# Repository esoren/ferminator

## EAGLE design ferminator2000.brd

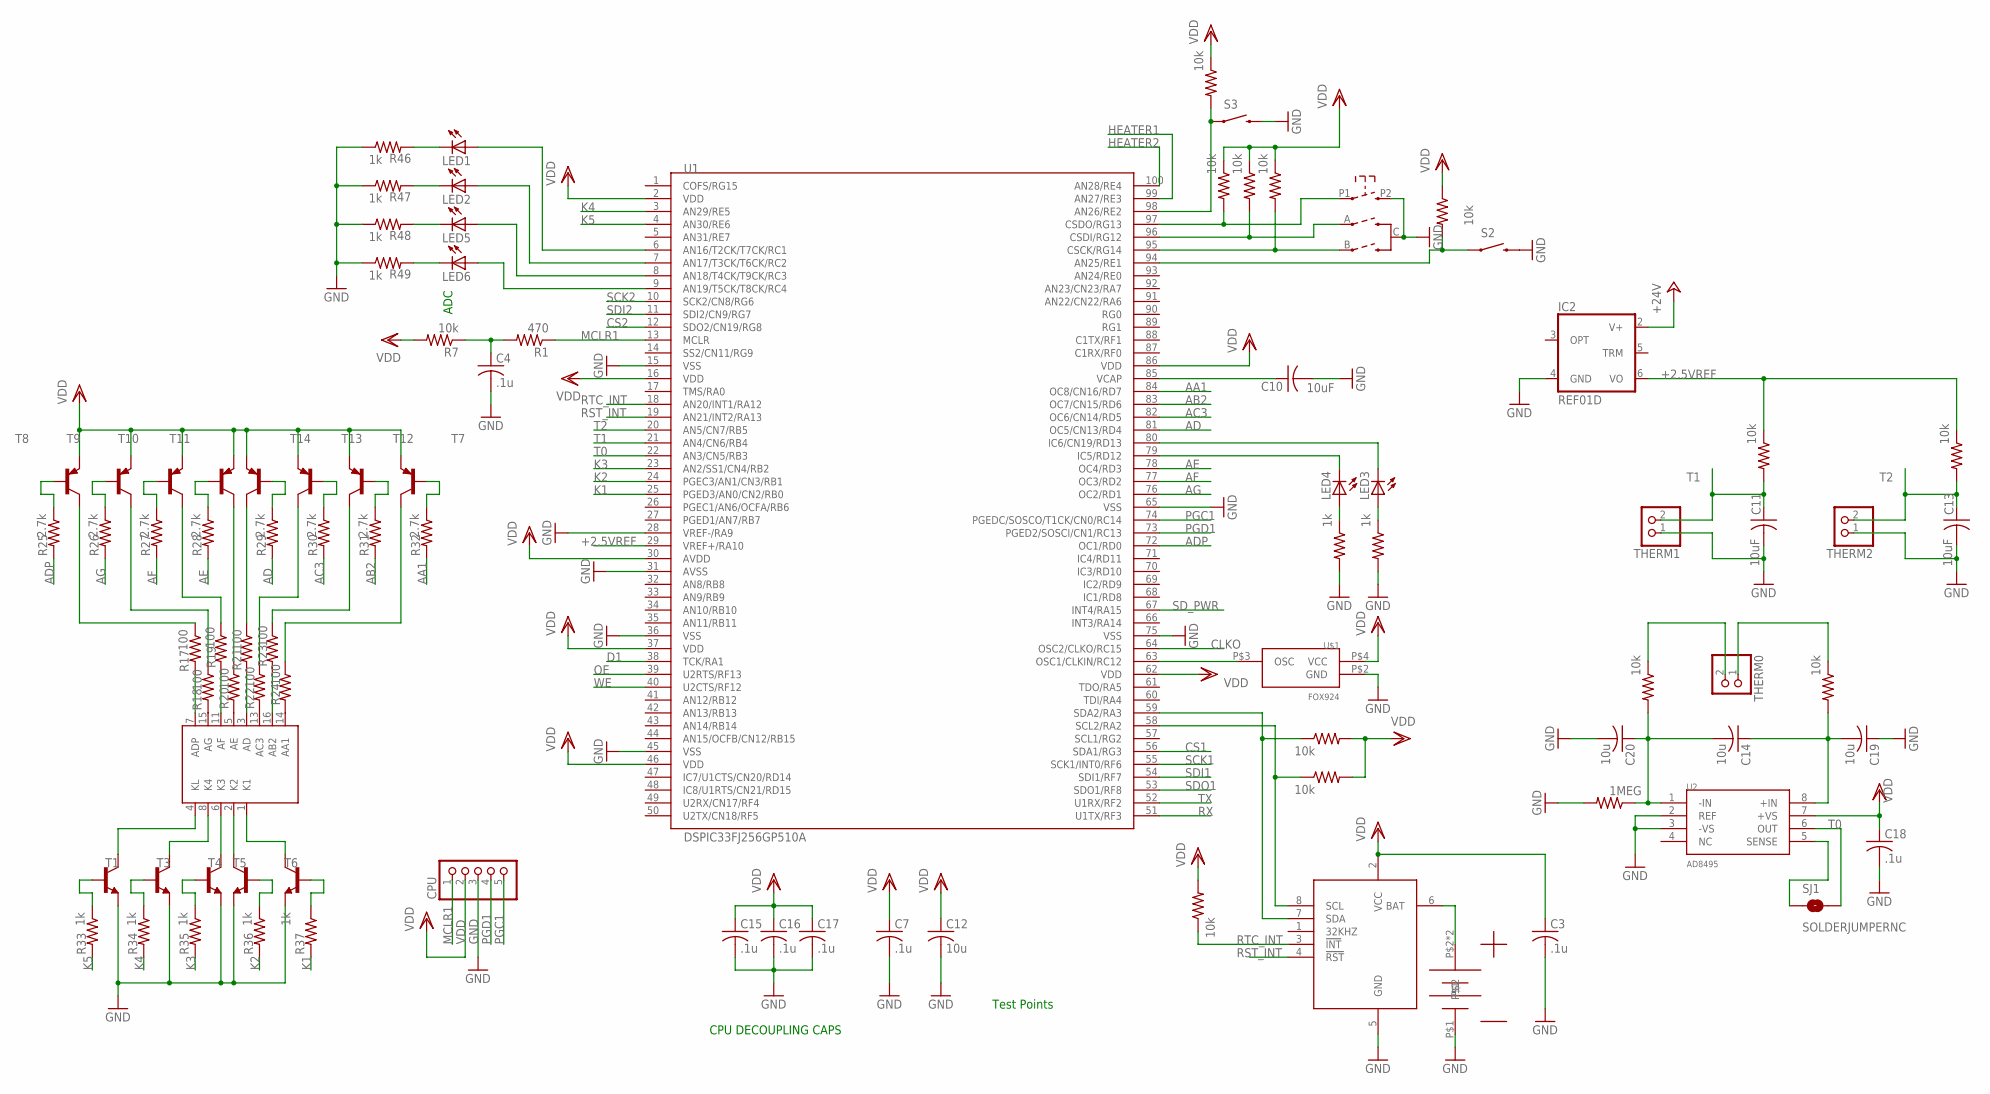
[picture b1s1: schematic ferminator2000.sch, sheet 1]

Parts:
C3, C4, C7, C15, C16, C17, C18: .1u; C0603
C10, C11, C13: 10uF; C0805
C12: 10u; C0805
C14, C19, C20: 10u; C0603
CPU: PINHD-1X5; 1X05
IC2: REF01D; SO08
LED1, LED2, LED3, LED4, LED5, LED6: LEDCHIP-LED0805; CHIP-LED0805
R1: 470; R0805
R7, R38, R39, R41, R42, R43, R44, R45, R50, R51, R52, R53, R54: 10k; R0805
R14, R15, R33, R34, R35, R36, R37, R46, R47, R48, R49: 1k; R0805
R17, R18, R19, R20, R21, R22, R23, R24: 100; R0805
R25, R26, R27, R28, R29, R30, R31, R32: 2.7k; R0805
R40: 1MEG; R0805
S2, S3: SWITCH-MOMENTARY-2; TACTILE_SWITCH_TALL
SJ1: SOLDERJUMPERNC; SJ_2S
SW1: ENCODER_SW1-PEC12; PEC12_INCREMENTAL_ENCODER
T1, T3, T4, T5, T6: MMBT3904LT1-NPN-SOT23-BEC; SOT23-BEC
T7, T8, T9, T10, T11, T12, T13, T14: MMBT3906LT1-PNP-SOT23-BEC; SOT23-BEC
THERM0, THERM1, THERM2: PINHD-1X2; 1X02
U1: DSPIC33FJ256GP510A; TQFP100
U2: AD8495; MSOP8
U$1: FOX924; CRYSTAL
U$2: 12MM_BATTER_HOLDER; 12.5MMCOILCELLHOLDER
U$5: DS3231; SOIC8
U$7: LTC-4027JRLTC-4027JR; LTC-4727JR

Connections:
1: R17.1, T8.C
2: R18.1, T9.C
3: R19.1, T10.C
4: R20.1, T11.C
5: R21.1, T14.C
6: R22.1, T13.C
7: R23.1, T12.C
8: R24.1, T7.C
+2.5VREF: IC2.6 (VO), R38.1, R39.1, U1.29 (VREF+/RA10)
+24V: IC2.2 (V+); also elsewhere on the board
AA1: R32.2, U1.84 (OC8/CN16/RD7)
AA1_BASE: R32.1, T7.B
AB2: R31.2, U1.83 (OC7/CN15/RD6)
AB2_BASE: R31.1, T12.B
AC3: R30.2, U1.82 (OC6/CN14/RD5)
AC3_BASE: R30.1, T13.B
AD: R29.2, U1.81 (OC5/CN13/RD4)
ADP: R25.2, U1.72 (OC1/RD0)
ADP_BASE: R25.1, T8.B
AD_BASE: R29.1, T14.B
AE: R28.2, U1.78 (OC4/RD3)
AE_BASE: R28.1, T11.B
AF: R27.2, U1.77 (OC3/RD2)
AF_BASE: R27.1, T10.B
AG: R26.2, U1.76 (OC2/RD1)
AG_BASE: R26.1, T9.B
CLKIN: U1.63 (OSC1/CLKIN/RC12), U$1.P$3 (OSC)
CLKO: U1.64 (OSC2/CLKO/RC15)
CS1: U1.56 (SDA1/RG3); also elsewhere on the board
CS2: U1.12 (SDO2/CN19/RG8)
D1: U1.38 (TCK/RA1)
GND: C3.2, C4.2, C7.2, C10.2, C11.2, C12.2, C13.2, C15.2, C16.2, C17.2, C18.2, C19.1, C20.2, CPU.3, IC2.4 (GND), R14.2, R15.2, R40.2, R46.1, R47.1, R48.1, R49.1, S2.B2 (2), S3.B2 (2), SW1.C, SW1.P2 (2), T1.E, T3.E, T4.E, T5.E, T6.E, THERM1.1, THERM2.1, U1.15 (VSS), U1.28 (VREF-/RA9), U1.31 (AVSS), U1.36 (VSS), U1.45 (VSS), U1.65 (VSS), U1.75 (VSS), U2.2 (REF), U2.3 (-VS), U$1.P$2 (GND), U$2.P$1, U$5.5 (GND); also elsewhere on the board
HEATER1: U1.99 (AN27/RE3); also elsewhere on the board
HEATER2: U1.100 (AN28/RE4); also elsewhere on the board
K1: R37.2, U1.25 (PGED3/AN0/CN2/RB0)
K2: R36.2, U1.24 (PGEC3/AN1/CN3/RB1)
K3: R35.2, U1.23 (AN2/SS1/CN4/RB2)
K3_BASE: R35.1, T4.B
K4: R34.2, U1.3 (AN29/RE5)
K4_BASE: R34.1, T3.B
K5: R33.2, U1.4 (AN30/RE6)
K5_BASE: R33.1, T1.B
MCLR1: CPU.1, R1.1, U1.13 (MCLR)
unnamed: LED3.A, R14.1
unnamed: LED4.A, R15.1
unnamed: C4.1, R1.2, R7.1
unnamed: C10.1, U1.85 (VCAP)
unnamed: LED4.C, U1.79 (IC5/RD12)
unnamed: LED3.C, U1.80 (IC6/CN19/RD13)
unnamed: T1.C, U$7.4 (KL)
unnamed: U$2.P$2, U$2.P$3, U$5.6 (BAT)
unnamed: R45.1, U1.59 (SDA2/RA3), U$5.7 (SDA)
unnamed: T3.C, U$7.8 (K4)
unnamed: T4.C, U$7.6 (K3)
unnamed: T5.C, U$7.2 (K2)
unnamed: T6.C, U$7.1 (K1)
unnamed: R18.2, U$7.15 (AG)
unnamed: C14.2, C20.1, R40.1, R41.2, U2.1 (-IN)
unnamed: C14.1, C19.2, R42.2, U2.8 (+IN)
unnamed: R41.1, THERM0.2
unnamed: R42.1, THERM0.1
unnamed: R36.1, T5.B
unnamed: R37.1, T6.B
unnamed: SJ1.1, U2.5 (SENSE)
unnamed: R43.2, S3.A2 (1), U1.98 (AN26/RE2)
unnamed: R20.2, U$7.5 (AE)
unnamed: R22.2, U$7.13 (AC3)
unnamed: R24.2, U$7.14 (AA1)
unnamed: R17.2, U$7.7 (ADP)
unnamed: R19.2, U$7.11 (AF)
unnamed: R44.2, S2.A2 (1), U1.94 (AN25/RE1)
unnamed: R21.2, U$7.3 (AD)
unnamed: R23.2, U$7.16 (AB2)
unnamed: LED6.A, U1.9 (AN19/T5CK/T8CK/RC4)
unnamed: LED5.A, U1.8 (AN18/T4CK/T9CK/RC3)
unnamed: LED2.A, U1.7 (AN17/T3CK/T6CK/RC2)
unnamed: LED1.A, U1.6 (AN16/T2CK/T7CK/RC1)
unnamed: LED1.C, R46.2
unnamed: LED2.C, R47.2
unnamed: LED5.C, R48.2
unnamed: LED6.C, R49.2
unnamed: R52.2, SW1.B, U1.95 (CSCK/RG14)
unnamed: R50.2, SW1.A, U1.96 (CSDI/RG12)
unnamed: R51.2, SW1.P1 (1), U1.97 (CSDO/RG13)
unnamed: R53.1, U1.58 (SCL2/RA2), U$5.8 (SCL)
OE: U1.39 (U2RTS/RF13)
PGC1: CPU.5, U1.74 (PGEDC/SOSCO/T1CK/CN0/RC14)
PGD1: CPU.4, U1.73 (PGED2/SOSCI/CN1/RC13)
RST_INT: U1.19 (AN21/INT2/RA13), U$5.4 (!RST)
RTC_INT: R54.1, U1.18 (AN20/INT1/RA12), U$5.3 (!INT)
RX: U1.51 (U1TX/RF3); also elsewhere on the board
SCK1: U1.55 (SCK1/INT0/RF6); also elsewhere on the board
SCK2: U1.10 (SCK2/CN8/RG6)
SDI1: U1.54 (SDI1/RF7); also elsewhere on the board
SDI2: U1.11 (SDI2/CN9/RG7)
SDO1: U1.53 (SDO1/RF8); also elsewhere on the board
SD_PWR: U1.67 (INT4/RA15); also elsewhere on the board
T0: SJ1.2, U1.22 (AN3/CN5/RB3), U2.6 (OUT)
T1: C11.1, R38.2, THERM1.2, U1.21 (AN4/CN6/RB4)
T2: C13.1, R39.2, THERM2.2, U1.20 (AN5/CN7/RB5)
TX: U1.52 (U1RX/RF2); also elsewhere on the board
VDD: C3.1, C7.1, C12.1, C15.1, C16.1, C17.1, C18.1, CPU.2, R7.2, R43.1, R44.1, R45.2, R50.1, R51.1, R52.1, R53.2, R54.2, T7.E, T8.E, T9.E, T10.E, T11.E, T12.E, T13.E, T14.E, U1.2 (VDD), U1.16 (VDD), U1.30 (AVDD), U1.37 (VDD), U1.46 (VDD), U1.62 (VDD), U1.86 (VDD), U2.7 (+VS), U$1.P$4 (VCC), U$5.2 (VCC); also elsewhere on the board
WE: U1.40 (U2CTS/RF12)

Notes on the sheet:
ADC
CPU DECOUPLING CAPS
Test Points

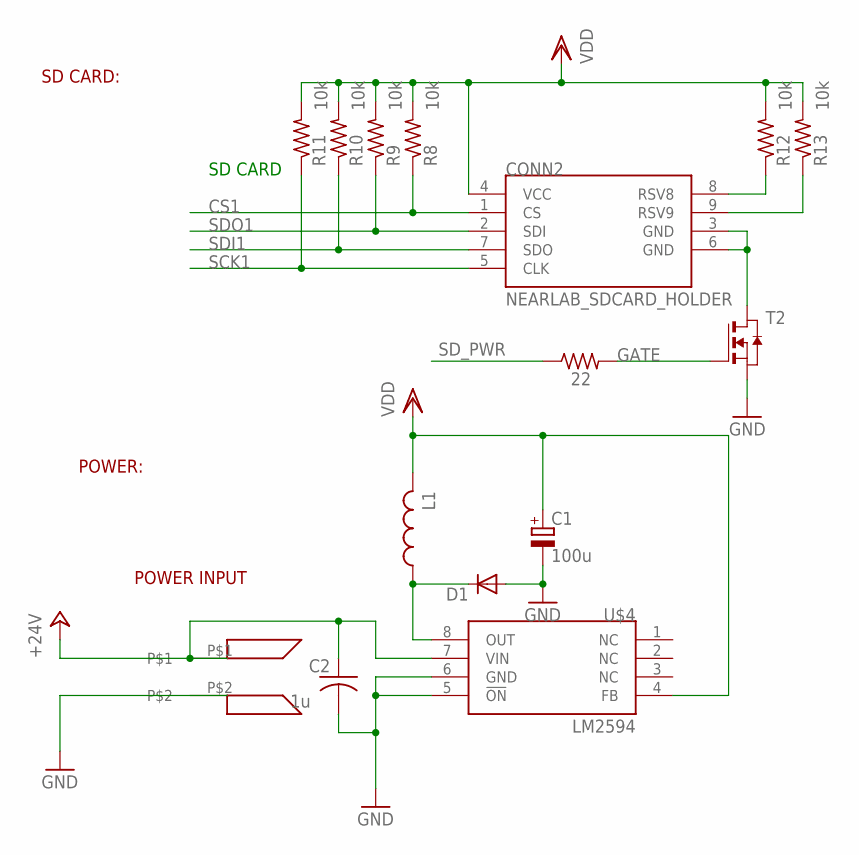
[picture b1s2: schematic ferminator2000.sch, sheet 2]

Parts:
C1: 100u; UD-6,3X5,8_NICHICON
C2: 1u; C0805
CONN2: NEARLAB_SDCARD_HOLDER; NEARLAB_DM1AA-SF-PEJ
D1: DIODE-SOD323-R; SOD323-R
L1: L-USL3225M; L3225M
R8, R9, R10, R11, R12, R13: 10k; R0805
R16: 22; R0805
T2: NMOSSOT23; SOT-23
U$3: PHOENIX-3.5MM; PHOENIX_3.5MM
U$4: LM2594; SOIC8

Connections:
+24V: C2.1, U$3.P$1, U$4.7 (VIN); also elsewhere on the board
CS1: CONN2.1 (CS), R8.1; also elsewhere on the board
GATE: R16.2, T2.3 (G)
GND: C1.-, C2.2, D1.A, T2.2 (S), U$3.P$2, U$4.5 (!ON), U$4.6 (GND); also elsewhere on the board
unnamed: CONN2.9 (RSV9), R13.1
unnamed: CONN2.8 (RSV8), R12.1
unnamed: CONN2.3 (GND), CONN2.6 (GND), T2.1 (D)
unnamed: D1.C, L1.1, U$4.8 (OUT)
SCK1: CONN2.5 (CLK), R11.1; also elsewhere on the board
SDI1: CONN2.7 (SDO), R10.1; also elsewhere on the board
SDO1: CONN2.2 (SDI), R9.1; also elsewhere on the board
SD_PWR: R16.1; also elsewhere on the board
VDD: C1.+, CONN2.4 (VCC), L1.2, R8.2, R9.2, R10.2, R11.2, R12.2, R13.2, U$4.4 (FB); also elsewhere on the board

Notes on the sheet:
SD CARD
SD CARD:
POWER:
POWER INPUT

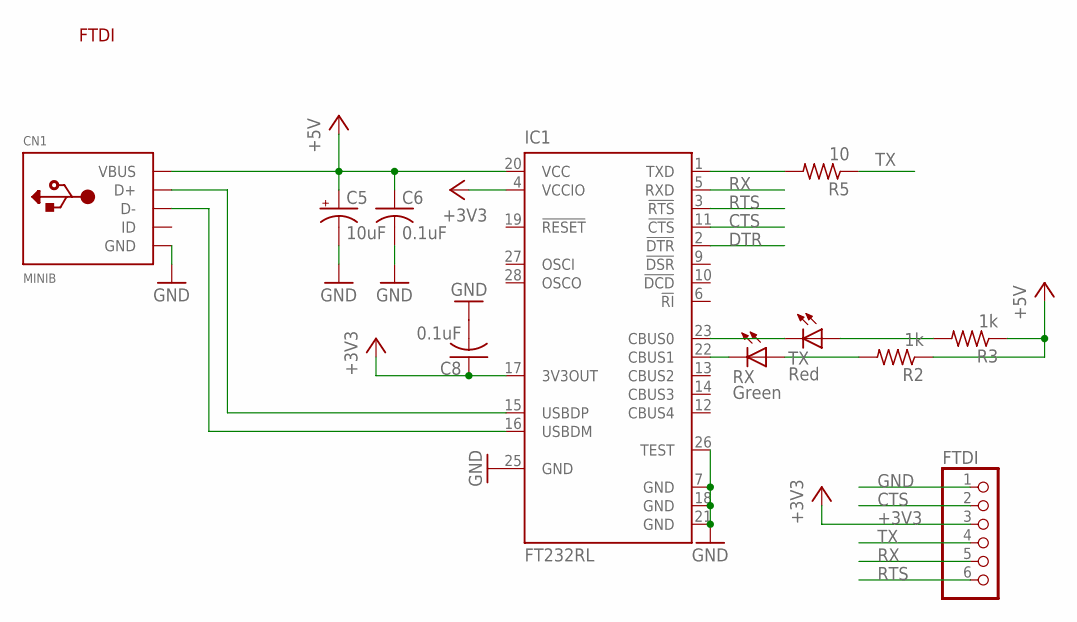
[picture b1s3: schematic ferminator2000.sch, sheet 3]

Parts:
C5: 10uF; A/3216-18R
C6, C8: 0.1uF; C0805K
CN1: MINIB; USB-MINIB
FTDI: PINHD-1X6CB; 1X06-CLEANBIG
IC1: FT232RL; SSOP28
R2, R3: 1k; R0805
R5: 10; R0805
RX: Green; CHIP-LED0805
TX: Red; CHIP-LED0805

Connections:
+3V3: C8.1, FTDI.3, IC1.4 (VCCIO), IC1.17 (3V3OUT)
+5V: C5.+, C6.1, CN1.VBUS, IC1.20 (VCC), R2.1, R3.1
CTS: FTDI.2, IC1.11 (!CTS)
DTR: IC1.2 (!DTR)
GND: C5.-, C6.2, C8.2, CN1.GND, FTDI.1, IC1.7 (GND), IC1.18 (GND), IC1.21 (GND), IC1.25 (GND), IC1.26 (TEST); also elsewhere on the board
unnamed: CN1.D+, IC1.15 (USBDP)
unnamed: CN1.D-, IC1.16 (USBDM)
unnamed: IC1.23 (CBUS0), TX.C
unnamed: IC1.22 (CBUS1), RX.C
unnamed: R2.2, RX.A
unnamed: R3.2, TX.A
unnamed: IC1.1 (TXD), R5.2
RTS: FTDI.6, IC1.3 (!RTS)
RX: FTDI.5, IC1.5 (RXD); also elsewhere on the board
TX: FTDI.4, R5.1; also elsewhere on the board

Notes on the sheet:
FTDI

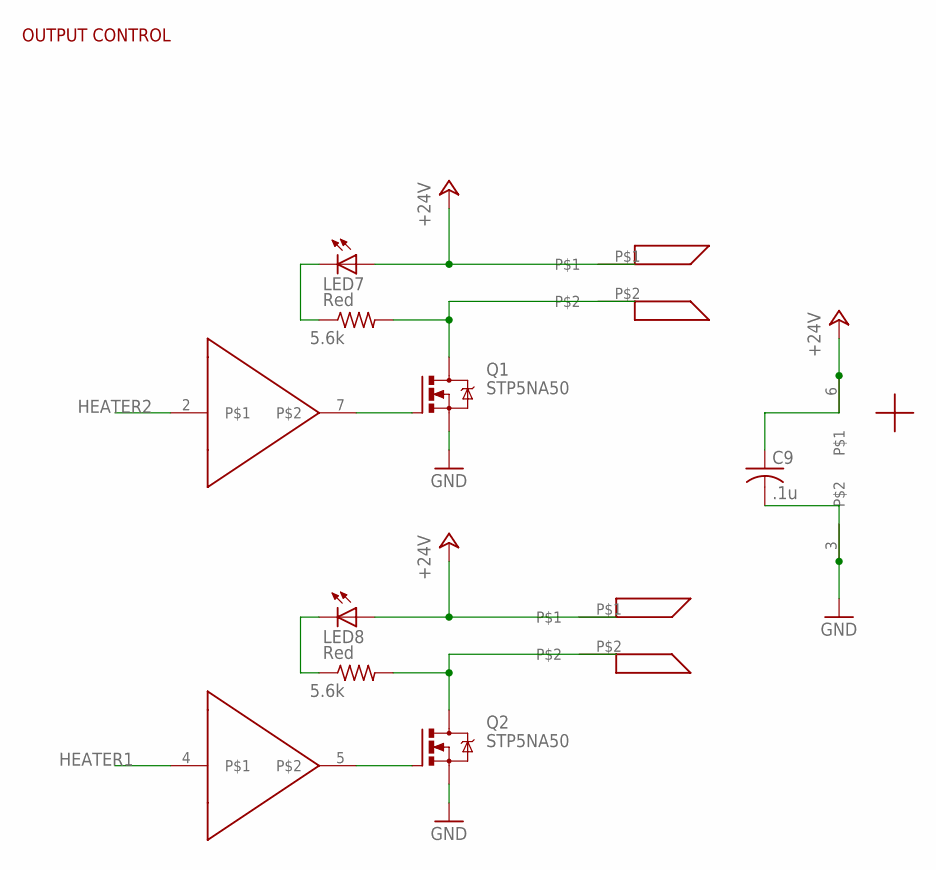
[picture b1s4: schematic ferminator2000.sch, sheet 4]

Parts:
C9: .1u; C0603
LED7, LED8: Red; CHIP-LED0805
Q1, Q2: STP5NA50; TO220BV
R4, R6: 5.6k; R0805
U$8, U$10: PHOENIX-3.5MM; PHOENIX_3.5MM
U$11: TC4427; SOIC8

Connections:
+24V: C9.1, LED7.A, LED8.A, U$8.P$1, U$10.P$1, U$11.6; also elsewhere on the board
GND: C9.2, Q1.S, Q2.S, U$11.3; also elsewhere on the board
HEATER1: U$11.4; also elsewhere on the board
HEATER2: U$11.2; also elsewhere on the board
unnamed: Q1.D, R4.2, U$10.P$2
unnamed: Q1.G, U$11.7
unnamed: Q2.G, U$11.5
unnamed: LED7.C, R4.1
unnamed: Q2.D, R6.2, U$8.P$2
unnamed: LED8.C, R6.1

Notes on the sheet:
OUTPUT CONTROL

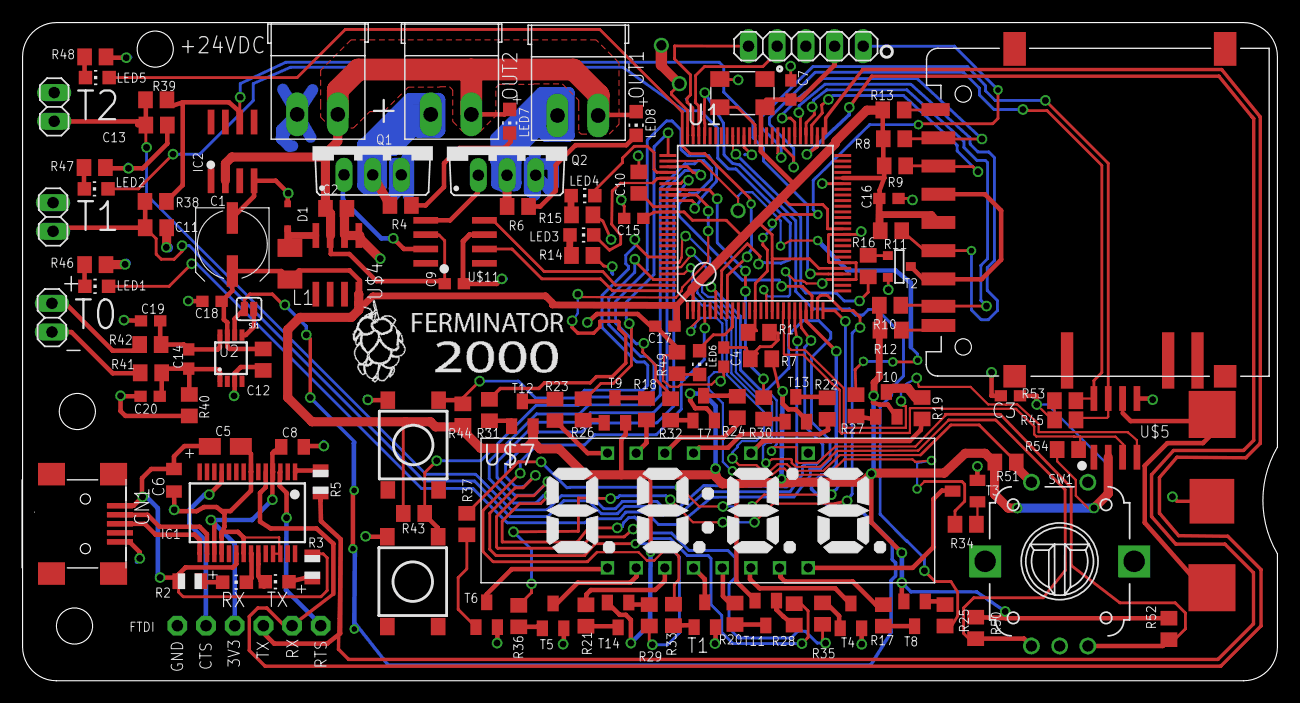
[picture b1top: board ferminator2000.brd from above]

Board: 2 copper layers, 111.1 x 58.3 mm, 126 parts (0 on the bottom side), 118 nets.

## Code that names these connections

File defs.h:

/*! \file defs.h
    \brief Contains all definitions
    
    
*/

#ifndef INC_DEFS_H
#define INC_DEFS_H


#define FCY 40000000UL ///40 MIPS operating speed (used for __delay_ms() and __delay_S())

#define BREAKPOINT Nop();Nop();Nop();
/** @defgroup LEDS LEDS
 * @{ */
#define T0_LED      LATCbits.LATC1
#define T0_LED_DIR  TRISCbits.TRISC1
#define T1_LED      LATCbits.LATC2
#define T1_LED_DIR  TRISCbits.TRISC2
#define T2_LED      LATCbits.LATC3
#define T2_LED_DIR  TRISCbits.TRISC3
#define LED3        LATDbits.LATD12
#define LED3_DIR    TRISDbits.TRISD12
#define LED4        LATDbits.LATD13
#define LED4_DIR    TRISDbits.TRISD13
#define LED6        LATCbits.LATC4
#define LED6_DIR     TRISCbits.TRISC4

/** @} */

/** @defgroup SD_PINS SD Pins
 * @{ */
#define SD_PWR 		LATAbits.LATA15
#define SD_PWR_DIR	TRISAbits.TRISA15		 
#define SDO1_PIN	LATFbits.LATF8
#define SDO1_PIN_DIR	TRISFbits.TRISF8
#define SDI1_PIN	PORTFbits.RF7
#define SDI1_PIN_DIR	TRISFbits.TRISF7
#define SCK1_PIN	LATFbits.LATF6
#define SCK1_PIN_DIR	TRISFbits.TRISF6
#define CS1_PIN		LATGbits.LATG3
#define CS1_PIN_DIR	TRISGbits.TRISG3
/** @} */

/** @defgroup HEATER_PINS HEATER Pins
 * @{ */
#define HEATER1_DIR     TRISEbits.TRISE3
#define HEATER1         LATEbits.LATE3
#define HEATER2_DIR     TRISEbits.TRISE4
#define HEATER2         LATEbits.LATE4

/** @} */


/** @defgroup ERROR_DEFS Error Definitions
 * @{ */
#define     GENERIC_ERROR			1 ///generic error flag
#define     SD_CARD_NOT_INITIALIZED		2 ///error initializing sd card
#define     BUFFER_OVERFLOW			3 ///buffer overflow
#define     BUFFER_POINTER			4 ///buffer pointer out of acceptable range
/** @} */

/** @defgroup TIMER_DEFS Timer Definitions
 * @{ */
#define TIMER2_ON		T2CONbits.TON  
#define TIMER2_PERIOD 	200   //3200 = 12.5KHz 1600 = 25KHz, 800 = 50KHz, 500 = 80KHz, 640 = 62.5Khz
/** @} */

// R1 Response Codes (from SD Card Product Manual v1.9 section 5.2.3.1)
/** @defgroup SD_DEFS SD Card Definitions
 * @{ */
#define R1_IN_IDLE_STATE        1		/// The card is in idle state and running initializing process.
#define R1_ERASE_RESET          (1<<1)  /// An erase sequence was cleared before executing because of an out of erase sequence command was received.
#define R1_ILLEGAL_COMMAND      (1<<2)  /// An illegal command code was detected
#define R1_COM_CRC_ERROR        (1<<3)  /// The CRC check of the last command failed.
#define R1_ERASE_SEQ_ERROR      (1<<4)  /// An error in the sequence of erase commands occured.
#define R1_ADDRESS_ERROR        (1<<5)  /// A misaligned address, which did not match the block length was used in the command.
#define R1_PARAMETER            (1<<6)  /// The command's argument (e.g. address, block length) was out of the allowed range for this card.
#define BLOCK_SIZE              512     ///sd card block size
#define BUFFER_SIZE             2048  /// size of the circular buffer
#define SD_START_ADDRESS        0      	///leave 10 KB at beginning of card for misc. information
#define CMD0_TIMEOUT            500    	///CMD0 timeout
#define CMD8_TIMEOUT            500     ///CMD8 timeout
#define CMD58_TIMEOUT           200     ///CMD58 timeout
#define ACMD41_CMD55_TIMEOUT    1000    ///ACMD41/CMD55 timeout (should take ~1 second)
#define CMD58_TIMEOUT2          1000    ///CMD58 timeout after initialization
#define START_BLOCK_TIMEOUT     10000   ///CMD17 start block timeout
#define MULTI_TOKEN_TIMEOUT     1000    ///CMD24 receive token timeout
#define PRE_ERASE_TIMEOUT       1000	///CMD55 pre-erase timeout
/** @} */


/** @defgroup ADC_DEFS ADC Definitions
 * @{ */
#define T2_DIR TRISBbits.TRISB5
#define T1_DIR TRISBbits.TRISB4
#define T0_DIR TRISBbits.TRISB3
#define T0_AN  3
#define T1_AN  4
#define T2_AN  5
#define ADC_SOURCE  AD1CHS0bits.CH0SA
#define ADC1_SAMP AD1CON1bits.SAMP


/** @} */

/** @defgroup SWITCHES Switches
 * @{ */
#define SW_SEL_DIR      TRISEbits.TRISE2
#define SW_SEL          PORTEbits.RE2
#define SW_SET_DIR      TRISEbits.TRISE1
#define SW_SET          PORTEbits.RE1
#define SW_ENC_A_DIR    TRISGbits.TRISG12
#define SW_ENC_A        PORTGbits.RG12
#define SW_ENC_B_DIR    TRISGbits.TRISG14
#define SW_ENC_B        PORTGbits.RG14
#define SW_ENC_PUSH_DIR TRISGbits.TRISG13
#define SW_ENC_PUSH     PORTGbits.RG13
/** @} */


/** @defgroup INTERRUPT_DEFS Interrupt Definitions
 * @{ */
#define DMA0_FLAG   IFS0bits.DMA0IF
#define DMA1_FLAG   IFS0bits.DMA1IF
#define DMA2_FLAG   IFS1bits.DMA2IF
#define TMR1_FLAG   IFS0bits.T1IF
#define TMR2_FLAG   IFS0bits.T2IF
#define TMR3_FLAG   IFS0bits.T3IF
#define DMA0_IE     IEC0bits.DMA0IE
#define DMA1_IE     IEC0bits.DMA1IE
#define TMR1_IE     IEC0bits.T1IE
#define TMR2_IE     IEC0bits.T2IE
#define TMR3_IE     IEC0bits.T3IE
/** @} */


/** @defgroup LCD_DISPLAY_DEFS LCD Display Definitions
 * @{ */
#define K1          LATBbits.LATB0
#define K1_DIR      TRISBbits.TRISB0
#define K2          LATBbits.LATB1
#define K2_DIR      TRISBbits.TRISB1
#define K3          LATBbits.LATB2
#define K3_DIR      TRISBbits.TRISB2
#define K4          LATEbits.LATE5
#define K4_DIR      TRISEbits.TRISE5
#define K5          LATEbits.LATE6
#define K5_DIR      TRISEbits.TRISE6

#define AA1         LATDbits.LATD7
#define AA1_DIR     TRISDbits.TRISD7
#define AB2         LATDbits.LATD6
#define AB2_DIR     TRISDbits.TRISD6
#define AC3         LATDbits.LATD5
#define AC3_DIR     TRISDbits.TRISD5
#define AD          LATDbits.LATD4
#define AD_DIR      TRISDbits.TRISD4
#define AE          LATDbits.LATD3
#define AE_DIR      TRISDbits.TRISD3
#define AF          LATDbits.LATD2
#define AF_DIR      TRISDbits.TRISD2
#define AG          LATDbits.LATD1
#define AG_DIR      TRISDbits.TRISD1
#define ADP         LATDbits.LATD0
#define ADP_DIR     TRISDbits.TRISD0

/** @} */


/** @defgroup RTC_DEFS RTC DEFS
 * @{ */

#define I2C2_SDA_PIN_DIR    TRISAbits.TRISA2
#define I2C2_SCL_PIN_DIR    TRISAbits.TRISA3
#define I2C2_SDA_PIN        LATAbits.LATA2
#define I2C2_SCL_PIN        LATAbits.LATA3



#define RTC_ADDRESS     0xD0

#define RTC_SECONDS     0x00
#define RTC_MINUTES     0x01
#define RTC_HOURS       0x02
#define RTC_DAY         0x03
#define RTC_DATE        0x04
#define RTC_MONTH       0x05
#define RTC_YEAR        0x06

#define RTC_A1_SECONDS  0x07
#define RTC_A1_MINUTES  0x08
#define RTC_A1_HOUR     0x09
#define RTC_A1_DAY      0x0A
#define RTC_A2_MINUTES  0x0B
#define RTC_A2_HOUR     0x0C
#define RTC_A2_DAY      0x0D

#define RTC_CONTROL     0x0E
#define RTC_STATUS      0x0F

#define RTC_AGING       0x10
#define RTC_TEMP_MSB    0x11
#define RTC_TEMP_LSB    0x12

/** @} */


#endif

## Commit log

2012-11-18 new file: ferminator2000.brd new file: ferminator2000.sch
2012-11-18 Added code from BEAD
2012-11-19 removed unused part of BEAD code
2012-11-19 added lcd_display()
2012-11-21 added pin definitions
2012-11-21 added bill of materials
2012-11-22 finished bom -- added parts from BEAD and smoothie
2012-11-28 Configured ADC module for T2
2012-11-28 Fixed Temperature Reading
2012-11-29 Added Control Lines for FETs
2012-12-04 added power to TC4427
2012-12-10 Added RTC to hardware
2013-08-12 Added battery and RTC chip
2013-11-14 Git Test
2013-11-19 Added pin 1 registration mark for RTC
2013-11-19 Added pin 1 registration mark for Crystal
2013-11-21 Added Pin 1 registration mark for TC4427
2013-11-21 Added Pin 1 registration mark for VREF
2013-11-21 Added R45, R53, and R54 to the BOM
2013-11-25 Added some I2C code for RTC
2013-11-26 Finished implementing I2C single-byte read test
2013-12-04 Added 0.1uF decoupling cap to RTC
2013-12-05 Added placeholder for RTC cap
2013-12-05 More I2C work..
2013-12-05 Tied REF pin of AD8495 (thermocouple driver) to ground
2013-12-05 Cleaned up code and added some comments to the ADC interrupt
2013-12-05 Added i2c source files
2014-01-15 Continuing work on I2C. i2c_read_byte is working well in this commit.
2014-01-15 I2C communication with RTC works with both 100KHz and 400KHz. Tested both i2c_write_byte() and i2c_read_byte().
2014-01-18 I2C and RTC tested fully. Time is logged and stored even with power removed.
2014-01-20 Fixed a major issue with SDHC cards initiating. This needs to get brought into the BEAD code as well.
2014-01-22 Code cleanup.
2014-01-24 Uart code added and tested.
2014-01-27 Added RTC files and read_time();
2014-01-27 Added RTC support. Reads from RTC, formats string, and writes it out to UART.
